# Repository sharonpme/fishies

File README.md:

# fishies

An automated fish feeder.

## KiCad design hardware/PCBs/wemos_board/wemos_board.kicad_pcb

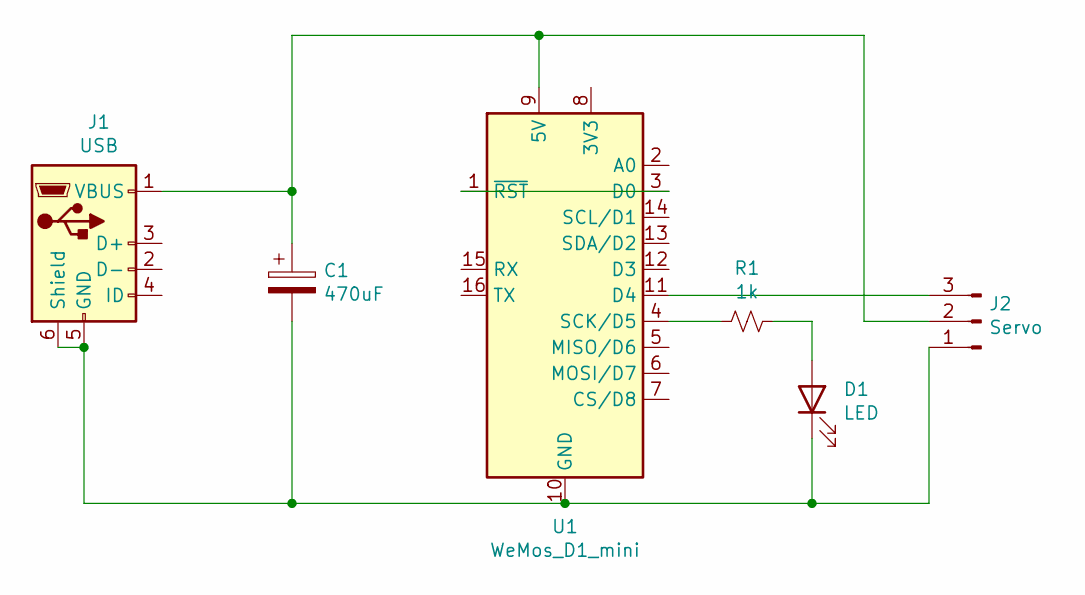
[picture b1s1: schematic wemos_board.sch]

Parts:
C1: 470uF; CP_Radial_D8.0mm_P2.50mm
D1: LED; JST_XH_B2B-XH-AM_1x02_P2.50mm_Vertical
J1: USB; USB_Micro-B_Molex_47346-0001
J2: Servo; PinHeader_1x03_P2.54mm_Vertical
R1: 1k; R_0805_2012Metric_Pad1.20x1.40mm_HandSolder
U1: WeMos_D1_mini; WEMOS_D1_mini_light

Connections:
unnamed: C1.1, J1.1 (VBUS), J2.2, U1.9 (5V)
unnamed: C1.2, D1.1 (K), J1.5 (GND), J1.6 (Shield), J2.1, U1.10 (GND)
unnamed: D1.2 (A), R1.1
unnamed: J2.3, U1.11 (D4)
unnamed: R1.2, U1.4 (SCK/D5)
unnamed: U1.1 (~RST), U1.3 (D0)

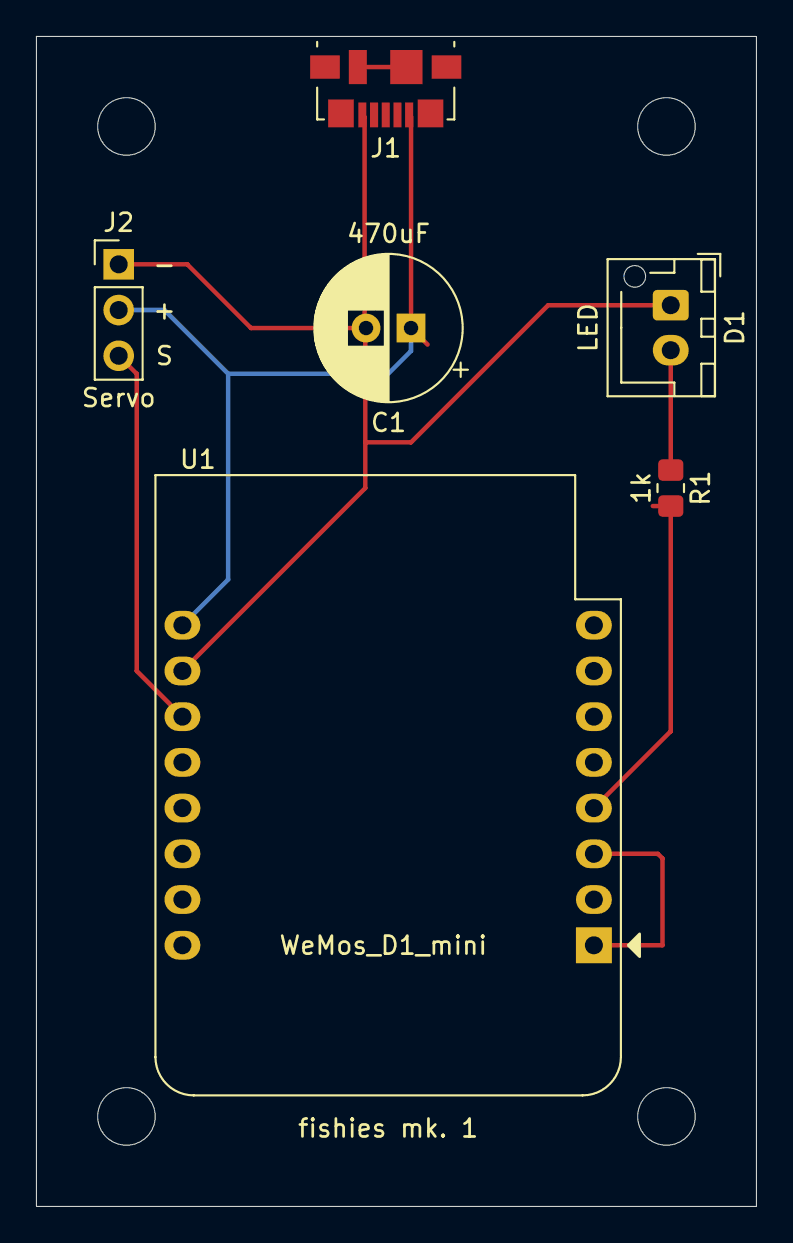
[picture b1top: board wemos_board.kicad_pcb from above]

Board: 2 copper layers, 40.0 x 65.0 mm, 6 parts (0 on the bottom side), 6 nets.

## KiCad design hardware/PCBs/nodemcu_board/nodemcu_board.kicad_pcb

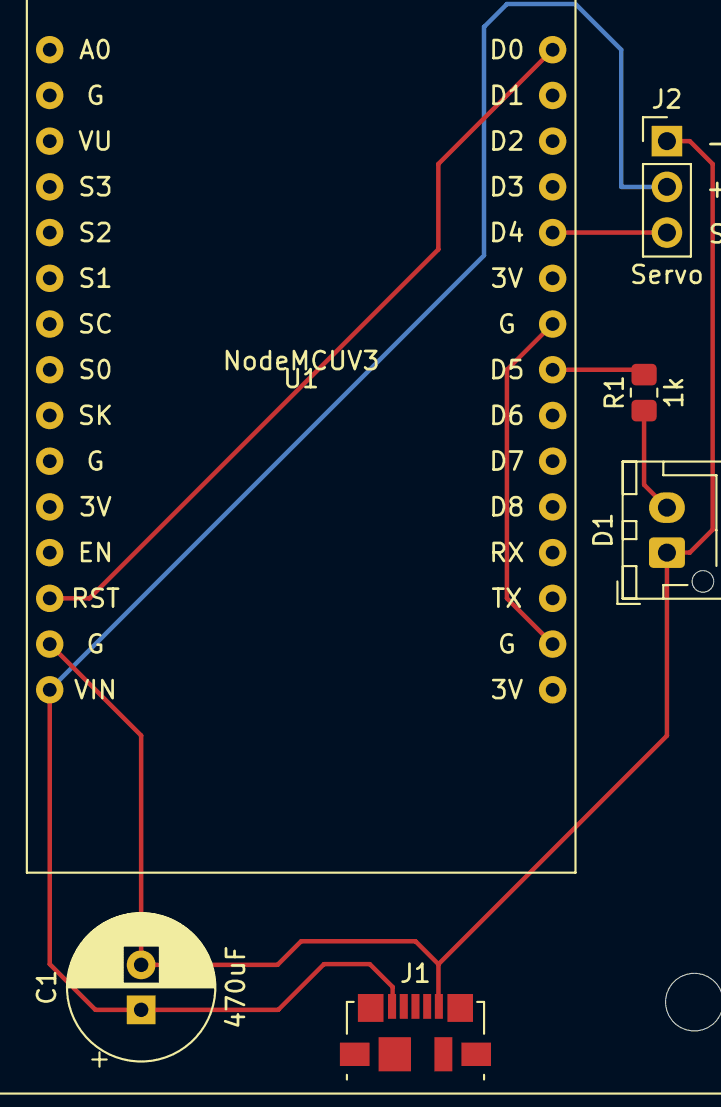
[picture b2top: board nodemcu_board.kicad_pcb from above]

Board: 2 copper layers, 6 parts (0 on the bottom side), 6 nets.

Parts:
C1: 470uF; CP_Radial_D8.0mm_P2.50mm
D1: LED; JST_XH_B2B-XH-AM_1x02_P2.50mm_Vertical
J1: USB; USB_Micro-B_Molex_47346-0001
J2: Servo; PinHeader_1x03_P2.54mm_Vertical
R1: 1k; R_0805_2012Metric_Pad1.20x1.40mm_HandSolder
U1: NodeMCUV3

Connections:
unnamed: C1.1, J1.1, J2.2, U1.14
unnamed: C1.2, D1.1, J1.5, J1.6, J2.1, U1.13
unnamed: D1.2, R1.1
unnamed: J2.3, U1.19
unnamed: R1.2, U1.22
unnamed: U1.12, U1.15

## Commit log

2021-06-24 Server readme
2021-06-24 timesync service for the server
2021-06-24 Updater
2021-06-24 README
2021-06-24 fix: Forgot to unhardcode server conf path in updater
2021-06-27 feat: vernemq compile and setup stuff
2021-06-28 feat: push server.conf
2021-06-28 feat: vernemq systemd unit
2021-06-28 fix: set vernemq env in systemd unit
2021-06-28 fix: fixed incorrect path in vernemq systemd execstart
2021-06-28 fix: fixed vernemq systemctl issues
2021-06-28 feat: mdns
2021-08-23 feat: scheduler
2021-08-24 feat: scheduler conf
2021-08-24 feat: scheduler conf 2
2021-08-24 feat: scheduler service
2021-08-24 fix: chmod +x scheduler/setup.sh
2021-08-24 feat: scheduler setup.sh setup systemd unit
2021-08-24 fix: scheduler setup.sh copy pages to etc and remove systemd syslog integration
2021-08-24 feat: scheduler setup.sh copy schedulers to etc
2021-08-24 feat: scheduler readme
2021-08-24 fix: renamed time timer unit
2021-08-24 fix: remove dependency on date
2021-08-24 fix: time improper systemd command
2021-08-24 fix: mdns chmod +x setup
2021-08-24 feat: logger
2021-08-24 fix: logger package lists
2021-08-25 feat: master setup script
2021-08-25 fix: chmod master setup
2021-08-26 fix: set retained flags to true
2021-08-26 fix:remove tmp build folder for vernemq
2021-08-27 fix: get logger working
2021-08-27 feat: logger csv output
2021-08-27 fix: typo in logger logstash pipeline
2021-08-27 feat: wemos pcb board
2021-08-27 feat: nodemcu pcb
2021-08-29 feat: add mdns to hosts
2021-08-29 fix: forgot to add domain to mqtt hosts
2021-08-30 feat: 3D Model
2021-08-30 fix: enabled systemd units in logger, scheduler and timer setup.sh
2021-08-31 fix: errors with 3D Models
2021-08-31 fix: misformed food disc carrier model
2021-08-31 fix: increased tolerance of the models to 0.8mm
2021-09-02 feat: micropython firmware
2021-09-02 feat: arduino firmware
2021-09-02 feat: BOM and CPL files for JLCPCB SMT fabrication
2021-09-02 fix: nodemcu_board fix footprints and added rst control line
2021-09-02 fix: wemos_board fix footprints and added rst control line
2021-09-03 feat: added svgs for laser cutting
